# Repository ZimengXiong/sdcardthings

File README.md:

# SD LED Card

SD-card-shaped RGB status module for a MacBook SD slot.

The intended UX is:

1. Insert the card.
2. macOS mounts a tiny volume.
3. Edit `LEDS.TXT` on that volume.
4. Firmware parses the written file and updates the LEDs.

This is not a passive SD adapter. The card has to emulate an SD memory card well
enough for macOS, then intercept block writes to a tiny virtual FAT volume.

## Current Direction

- Controller: RP2350/RP2350A, because PIO can emulate 4-bit SDIO timing.
- SD behavior: fork/adapt `petritoast/pico_sdcard`.
- LED control: low-profile RGB LEDs on the exposed end of the SD card.
- Storage model: virtual FAT volume with a fixed `LEDS.TXT`.
- First hardware: full-size SD card outline, 3.3 V only, no UHS-II.

## Important Constraint

A microcontroller cannot simply "read a file on the SD card" while the Mac is
also using that same SD storage bus. SD is host-owned. To make the file workflow
work smoothly, our MCU should be the SD card: it emulates the block device,
accepts writes from macOS, and updates LEDs when the file content changes.

The alternate approach is a real microSD card plus bus switch, but that usually
requires the Mac to unmount/eject before the MCU can safely read the card. That
is a worse UX for this project.

## Repo Layout

- `docs/architecture.md` - technical plan and tradeoffs.
- `hardware/` - KiCad and hardware notes.
- `firmware/led_config/` - parser for `LEDS.TXT`.
- `firmware/pico_sdcard_upstream/` - upstream SD emulator reference.

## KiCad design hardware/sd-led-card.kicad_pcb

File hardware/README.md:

# Hardware Notes

## First PCB Revision

Build a full-size SD-card-shaped board that is electrically conservative:

- 3.3 V signaling only.
- SD default speed first.
- No UHS-II contacts.
- ENIG edge contacts.
- Low-current LEDs.
- Test pads for SWD/programming.

Current generated PCB status:

- KiCad DRC: clean, 0 violations / 0 unconnected items.
- KiCad ERC: 0 errors. Remaining warnings are library-table/config warnings
  from generated embedded `SDLED` symbols and an intentionally isolated
  `BOOTSEL` debug pad.
- The schematic now captures the intended electrical blocks: SD edge contacts,
  RP2350A, chained addressable side LEDs, capacitive touch, decoupling, and
  SWD/debug pads.
- The current PCB includes a debug-only breakaway probe tail. It extends past
  the exposed end of the SD card and brings the nine SD edge contacts out to
  larger probe pads so host/card behavior can be observed while inserted.
- Components are placed on the same face as the SD contact pads.
- Decorative no-net routing has been removed.
- The remaining production gates are exact LED part/footprint selection, final
  routed copper, exact manufacturer stackup, and confirmed component heights
  for the target MacBook SD slot.

## Mechanical Z Budget

This design is based on KiCad's `SD_Card_Device_16mm_SlotDepth` footprint. That
template models the inserted contact/mechanical region of a full-size SD card.
For the component stack to fit under normal full-size SD thickness, this design
targets a **0.8 mm PCB** rather than the template's original 1.4 mm note.

The current placement keeps component bodies outside that inserted 16 mm region:

| Item | Side | Approx. package height | Mechanical note |
| --- | --- | ---: | --- |
| RP2350A QFN-60 | SD-contact side | 0.90 mm max | About 1.70 mm total on a 0.8 mm PCB. |
| EASV3015RGBA0 right-angle LED | SD-contact side | 1.10 mm max | About 1.90 mm total on a 0.8 mm PCB. |
| 0402 capacitors | SD-contact side | about 0.5 mm | About 1.30 mm total on a 0.8 mm PCB. |
| CT1 capacitive touch electrode | SD-contact side | bare copper | No component height. |
| Debug/test pads | SD-contact side | bare copper | Mechanically safe; no component height. |

The 0.8 mm stack makes the current known package heights fit below the normal
2.1 mm SD-card thickness. This revision intentionally does **not** use a local
stiffener or thickness buildup, because that complicates fabrication. The main
remaining mechanical risk is contact reliability: a 0.8 mm rigid PCB may be
too thin for some SD-slot spring contacts even if it physically inserts cleanly.

The next practical step is a cheap bare-board/mechanical coupon with ENIG edge
pads. Test insertion, removal, pad contact, and whether the side LEDs remain
visible in the target Mac slot before committing to an assembled run.

For bring-up, order the debug-tail Gerbers first. The tail is not part of the
final card; cut or flex off the narrow neck after probing, then lightly smooth
the exposed edge. Do not use the debug-tail board as the final mechanical fit
answer until the snapped edge has been cleaned up and rechecked in the slot.

Run `tools/check_mechanical_envelope.py` after regenerating the board. It fails
if any known package body is placed inside the inserted 16 mm SD-slot region or
if any known board-plus-package stack exceeds normal SD card thickness.

## Candidate Pin Map

This follows the upstream RP2350 SD emulator default:

| Signal | RP2350 GPIO |
| --- | ---: |
| SD CMD | GP0 |
| SD CLK | GP1 |
| SD DAT0 | GP2 |
| SD DAT1 | GP3 |
| SD DAT2 | GP4 |
| SD DAT3 | GP5 |
| LED DATA | GP6 |
| CAP TOUCH | GP7 |

## Mechanical Notes

Use KiCad's SD-card-device footprint as the starting point for outline and edge
pads. The exposed end should contain the LED diffuser windows and any touch
electrode. Keep all components out of the deep-insertion region unless a real
slot-clearance check proves there is room.

The current capacitive touch electrode is `CT1`, a bare copper/ENIG pad on the
SD-contact side near the exposed lip. It should route to `GP7` through the
touch-sensing front end. Keep a local ground guard optional for a later rev:
the first board should prioritize a large accessible touch area and tune
thresholds in firmware.

## BOM Direction

- MCU: RP2350A/RP2350B, final package TBD by routing and thickness.
- LEDs: right-angle / side-view RGB LEDs facing the exposed SD-card lip. A
  top-emitting addressable LED is a poor fit here unless we add a real light
  pipe, because the laptop slot hides most of the top face.
- Decoupling: local 100 nF caps at MCU and LEDs, plus small bulk capacitance.
- Optional ESD: low-capacitance ESD array on exposed SD lines.

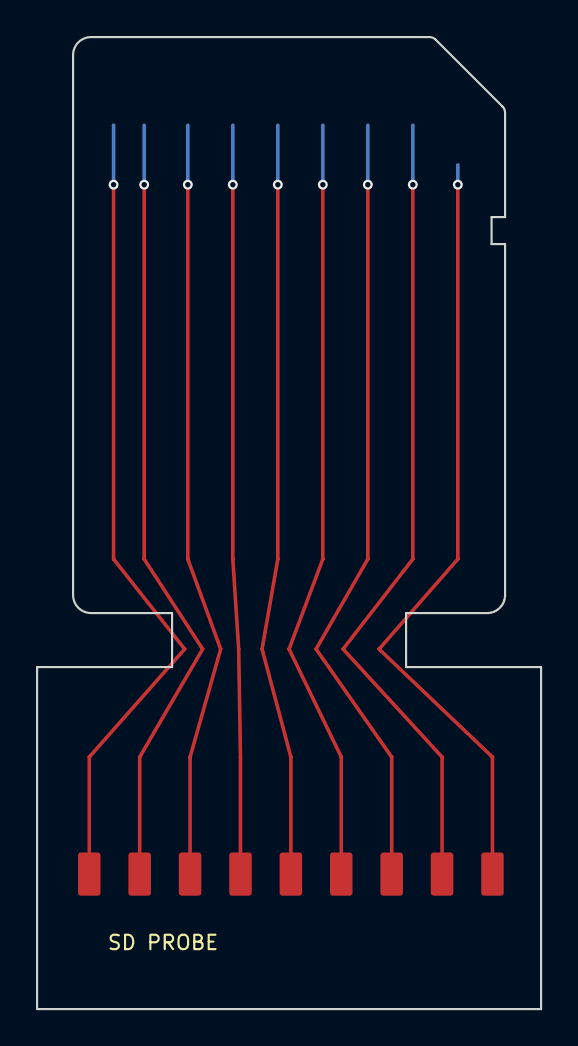
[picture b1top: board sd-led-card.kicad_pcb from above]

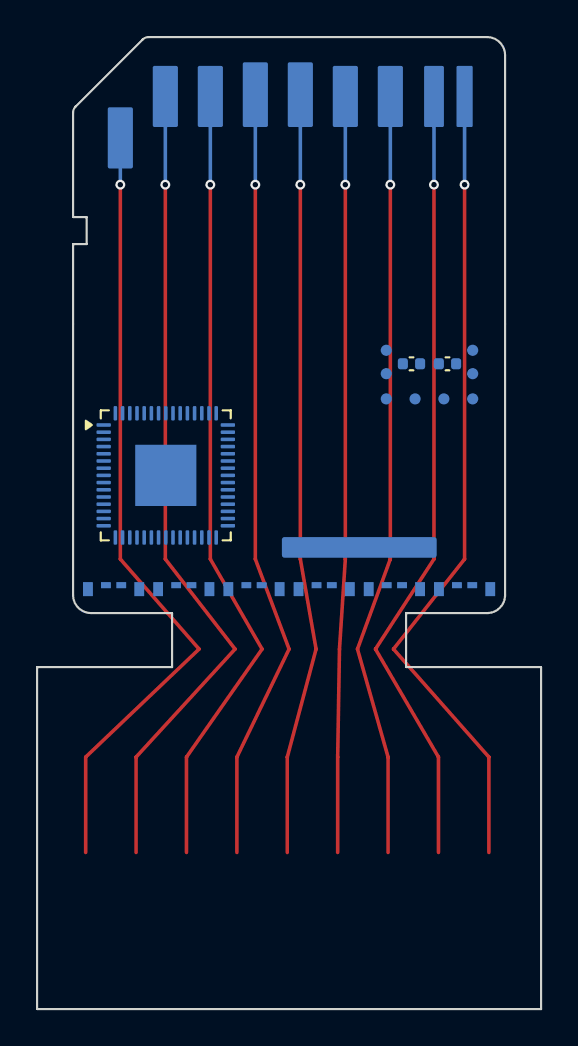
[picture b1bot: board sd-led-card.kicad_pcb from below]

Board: 2 copper layers, 28.0 x 54.0 mm, 13 parts (11 on the bottom side), 9 nets.

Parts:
C1: 100n; C_0402_1005Metric
C2: 1u; C_0402_1005Metric
CT1: CT1
D1, D2, D3, D4, D5, D6: EASV3015 side RGB; LED_RGB_Everlight_EASV3015RGBA0_Horizontal
DBG1: SWD/debug pads
J1: SD card edge contacts; SD_Card_Device_16mm_SlotDepth
J2: breakaway SD probe pads
U1: RP2350A; QFN-60-1EP_7x7mm_P0.4mm_EP3.4x3.4mm

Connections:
+3V3: J1.4, J2.4
GND: J1.6, J2.6
SD_CLK: J1.5, J2.5
SD_CMD: J1.3, J2.3
SD_DAT0: J1.7, J2.7
SD_DAT1: J1.8, J2.8
SD_DAT2: J1.1, J2.1
SD_DAT3: J1.2, J2.2
SD_VSS2: J1.9, J2.9

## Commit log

2026-05-26 Initial SD LED card design
2026-05-26 Move edge LEDs closer
2026-05-26 Rebase layout on SD card footprint
2026-05-26 Add SD slot height envelope check
2026-05-26 Target thin PCB for SD slot fit
2026-05-26 Document SD slot stiffener envelope
2026-05-27 Add functional schematic scaffold
2026-05-27 Remove contact stiffener assumption
2026-05-27 Add bare board Gerber package
2026-05-27 Add breakaway SD probe tail
